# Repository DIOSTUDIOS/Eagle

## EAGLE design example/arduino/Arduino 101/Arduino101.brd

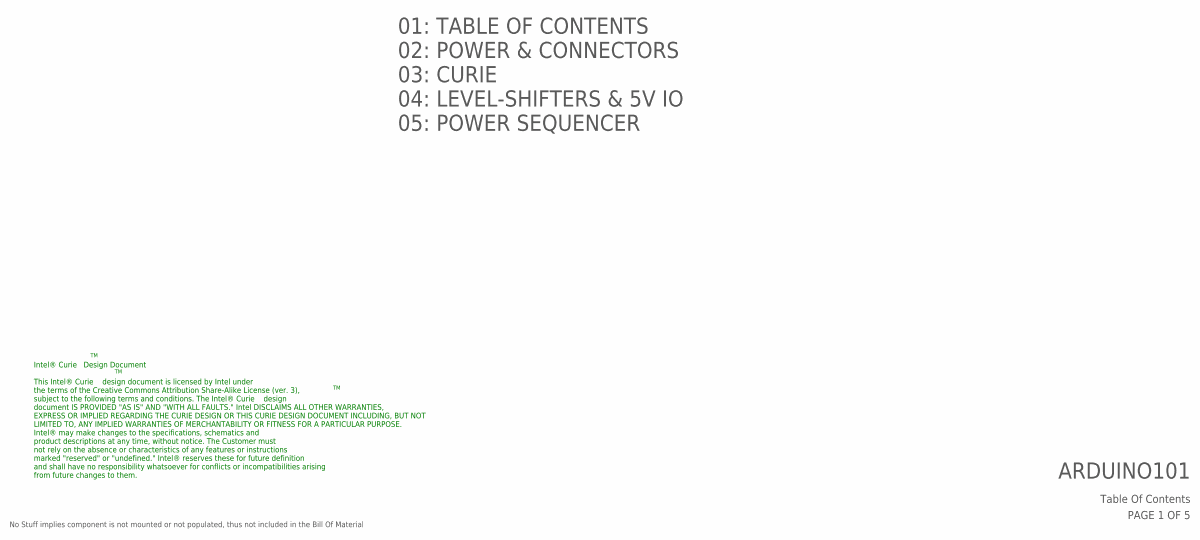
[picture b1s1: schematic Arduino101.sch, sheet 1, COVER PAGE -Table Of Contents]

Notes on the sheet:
Table Of Contents
PAGE 1 OF 5
ARDUINO101
No Stuff implies component is not mounted or not populated, thus not included in the Bill Of Material
01: TABLE OF CONTENTS
02: POWER & CONNECTORS
03: CURIE
04: LEVEL-SHIFTERS & 5V IO
05: POWER SEQUENCER
Intel® Curie Design Document This Intel® Curie design document is licensed by Intel under the terms of the Creative Commons Attribution Share-Alike License (ver. 3), subject to the following terms and conditions. The Intel® Curie design document IS PROVIDED "AS IS" AND "WITH ALL FAULTS." Intel DISC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

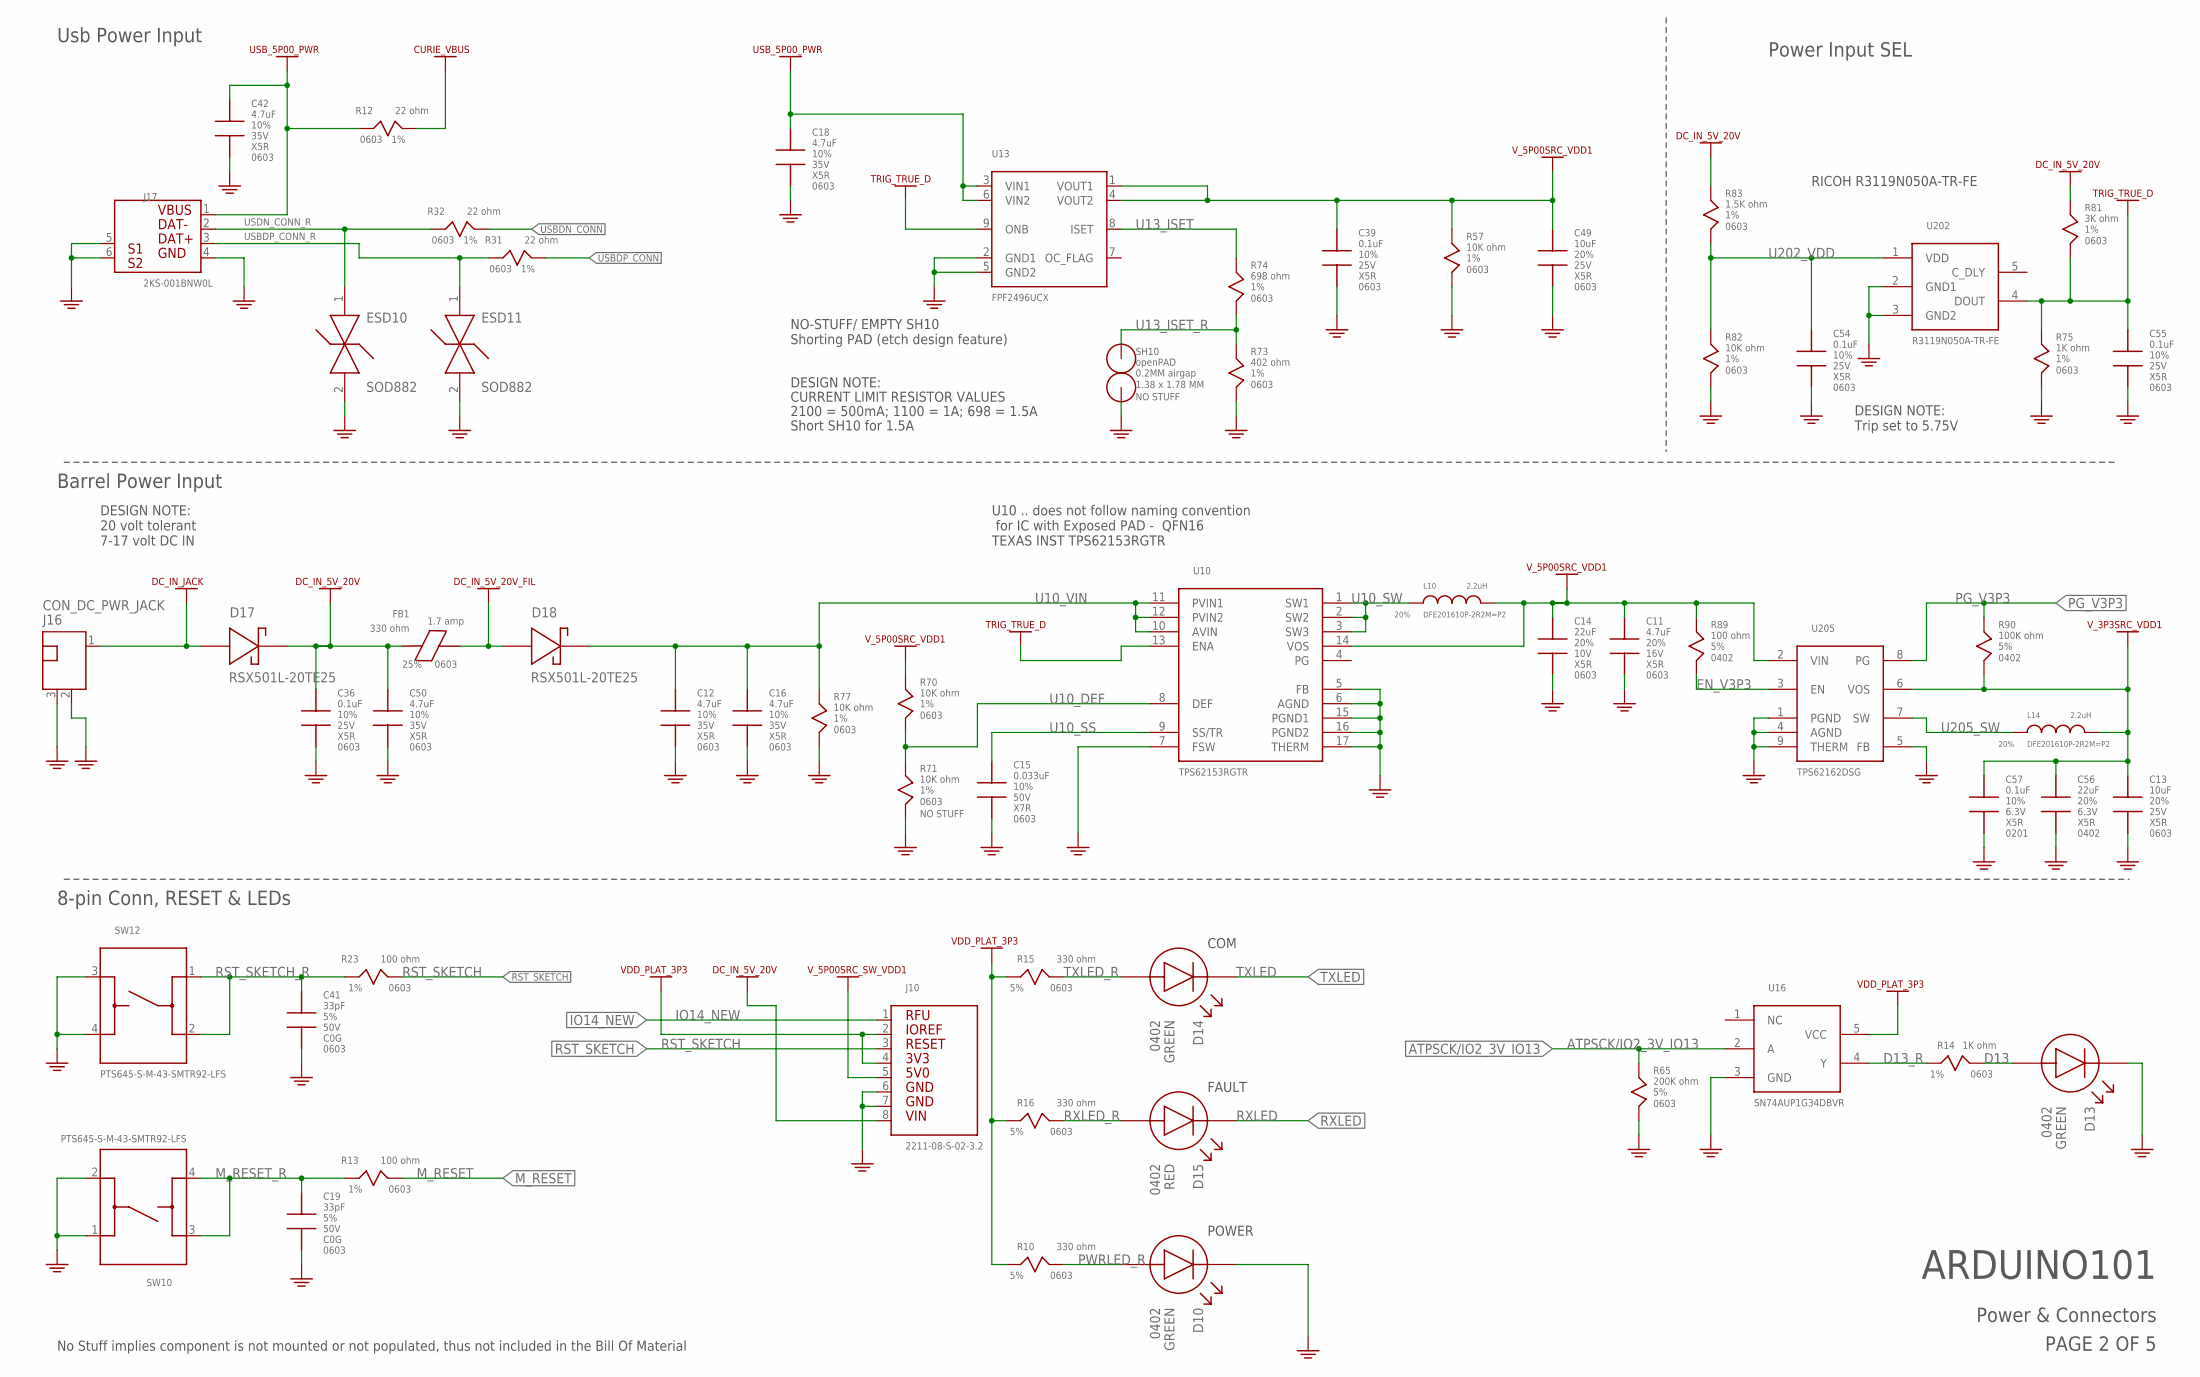
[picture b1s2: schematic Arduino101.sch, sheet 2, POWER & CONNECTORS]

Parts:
C11, C12, C16, C18, C42, C50: 4.7uF; 0603X90H
C13, C49: 10uF; 0603X90H
C14: 22uF; 0603X90H
C15: 0.033uF; 0603X90H
C19, C41: 33pF; 0603X90H
C36, C39, C54, C55: 0.1uF; 0603X90H
C56: 22uF; CAP0402
C57: 0.1uF; CAP0201
D10, D13, D14: LED_SML-P12PTT86; LED_100X60X25H_SMLP13
D15: LED_SML-P11UTT86; LED_100X60X25H_SMLP13
D17, D18: DIO_RSX501L-20TE25; DIO2_450X260X220H
ESD10, ESD11: PESD5V0X1BCAL,315; DIO_SOD882
FB1: FERRITE_BEAD_0603_BLM18KG331SN1D; 0603X90H
J10: CON_1X8_2211-08-S-02-3.2; CONF1X8-254P_2104X240X850H_TH
J16: CON_DC_PWR_JACK; CON_JACK_880X1350X1135H_EJ508A
J17: CON_USB_TYPE_B; CON_USB_1204X1650X1115_AUY1007
L10, L14: 2.2uH; 0806X100H
R10, R15, R16: 330 ohm; 0603X90H
R12, R31, R32: 22 ohm; 0603X90H
R13, R23: 100 ohm; 0603X90H
R14, R75: 1K ohm; 0603X90H
R57, R70, R71, R77, R82: 10K ohm; 0603X90H
R65: 200K ohm; 0603X90H
R73: 402 ohm; 0603X90H
R74: 698 ohm; 0603X90H
R81: 3K ohm; 0603X90H
R83: 1.5K ohm; 0603X90H
R89: 100 ohm; SMR0402
R90: 100K ohm; SMR0402
SH10: openPAD; SHORT_140X180
SW10, SW12: SWITCH_PTS645-S-M-43-SMTR92-LFS; SW4_600X600X430H_SM_PTS645
U10: TPS62153RGTR; QFN16-50P_300X300X100H_TR
U13: FPF2496UCX_WLCSP_VREG; BGA9_3X3-40P_121X121X63H
U16: SN74AUP1G34DBVR; SOT23-5_160X290X145H
U202: R3119-VREG; SOT23-5_160X290X120H
U205: TPS62162DSG; USON8_5MM_2X2MM-DIE

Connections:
ATPSCK/IO2_3V_IO13: R65.1, U16.2 (A); also elsewhere on the board
CURIE_VBUS: R12.2; also elsewhere on the board
D13: D13.1 (A), R14.2
D13_R: R14.1, U16.4 (Y)
DC_IN_5V_20V: C36.1, C50.1, D17.1, FB1.1, J10.8, R81.1, R83.1
DC_IN_5V_20V_FIL: D18.2, FB1.2
DC_IN_JACK: D17.2, J16.1; also elsewhere on the board
EN_V3P3: R89.2, U205.3 (EN)
GND: C11.2, C12.2, C13.2, C14.2, C15.2, C16.2, C18.2, C19.2, C36.2, C39.2, C41.2, C42.2, C49.2, C50.2, C54.2, C55.2, C56.2, C57.2, D10.2 (K), D13.2 (K), ESD10.2, ESD11.2, J10.6, J10.7, J16.2, J16.3, J17.4, J17.5, J17.6, R57.2, R65.2, R71.2, R73.2, R75.2, R77.2, R82.2, SH10.2, SW10.1, SW10.2, SW12.3, SW12.4, U10.5 (FB), U10.6 (AGND), U10.7 (FSW), U10.15 (PGND1), U10.16 (PGND2), U10.17 (THERM), U13.2 (GND1), U13.5 (GND2), U16.3 (GND), U202.2 (GND1), U202.3 (GND2), U205.1 (PGND), U205.4 (AGND), U205.5 (FB), U205.9 (THERM); also elsewhere on the board
IO14_NEW: J10.1; also elsewhere on the board
M_RESET: R13.2; also elsewhere on the board
M_RESET_R: C19.1, R13.1, SW10.3, SW10.4
PG_V3P3: R90.1, U205.8 (PG); also elsewhere on the board
PWRLED_R: D10.1 (A), R10.2
RST_SKETCH: J10.3, R23.2; also elsewhere on the board
RST_SKETCH_R: C41.1, R23.1, SW12.1, SW12.2
RXLED: D15.2 (K); also elsewhere on the board
RXLED_R: D15.1 (A), R16.2
TRIG_TRUE_D: C55.1, R75.1, R81.2, U10.13 (ENA), U13.9 (ONB), U202.4 (DOUT)
TXLED: D14.2 (K); also elsewhere on the board
TXLED_R: D14.1 (A), R15.2
U10_DEF: R70.2, R71.1, U10.8 (DEF)
U10_SS: C15.1, U10.9 (SS/TR)
U10_SW: L10.1, U10.1 (SW1), U10.2 (SW2), U10.3 (SW3)
U10_VIN: C12.1, C16.1, D18.1, R77.1, U10.10 (AVIN), U10.11 (PVIN1), U10.12 (PVIN2)
U13_ISET: R74.1, U13.8 (ISET)
U13_ISET_R: R73.1, R74.2, SH10.1
U202_VDD: C54.1, R82.1, R83.2, U202.1 (VDD)
U205_SW: L14.1, U205.7 (SW)
USBDN_CONN: R32.2; also elsewhere on the board
USBDP_CONN: R31.2; also elsewhere on the board
USBDP_CONN_R: ESD11.1, J17.3, R31.1
USB_5P00_PWR: C18.1, C42.1, J17.1, R12.1, U13.3 (VIN1), U13.6 (VIN2); also elsewhere on the board
USDN_CONN_R: ESD10.1, J17.2, R32.1
VDD_PLAT_3P3: J10.2, J10.4, R10.1, R15.1, R16.1, U16.5 (VCC); also elsewhere on the board
V_3P3SRC_VDD1: C13.1, C56.1, C57.1, L14.2, R90.2, U205.6 (VOS); also elsewhere on the board
V_5P00SRC_SW_VDD1: J10.5; also elsewhere on the board
V_5P00SRC_VDD1: C11.1, C14.1, C39.1, C49.1, L10.2, R57.1, R70.1, R89.1, U10.14 (VOS), U13.1 (VOUT1), U13.4 (VOUT2), U205.2 (VIN); also elsewhere on the board

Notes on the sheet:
Power & Connectors
PAGE 2 OF 5
ARDUINO101
Barrel Power Input
DESIGN NOTE:
CURRENT LIMIT RESISTOR VALUES
2100 = 500mA; 1100 = 1A; 698 = 1.5A
Usb Power Input
No Stuff implies component is not mounted or not populated, thus not included in the Bill Of Material
8-pin Conn, RESET & LEDs
Power Input SEL
DESIGN NOTE: Trip set to 5.75V
Short SH10 for 1.5A
DESIGN NOTE: 20 volt tolerant 7-17 volt DC IN
COM
FAULT
POWER
NO-STUFF/ EMPTY SH10 Shorting PAD (etch design feature)
RICOH R3119N050A-TR-FE
U10 .. does not follow naming convention for IC with Exposed PAD - QFN16 TEXAS INST TPS62153RGTR

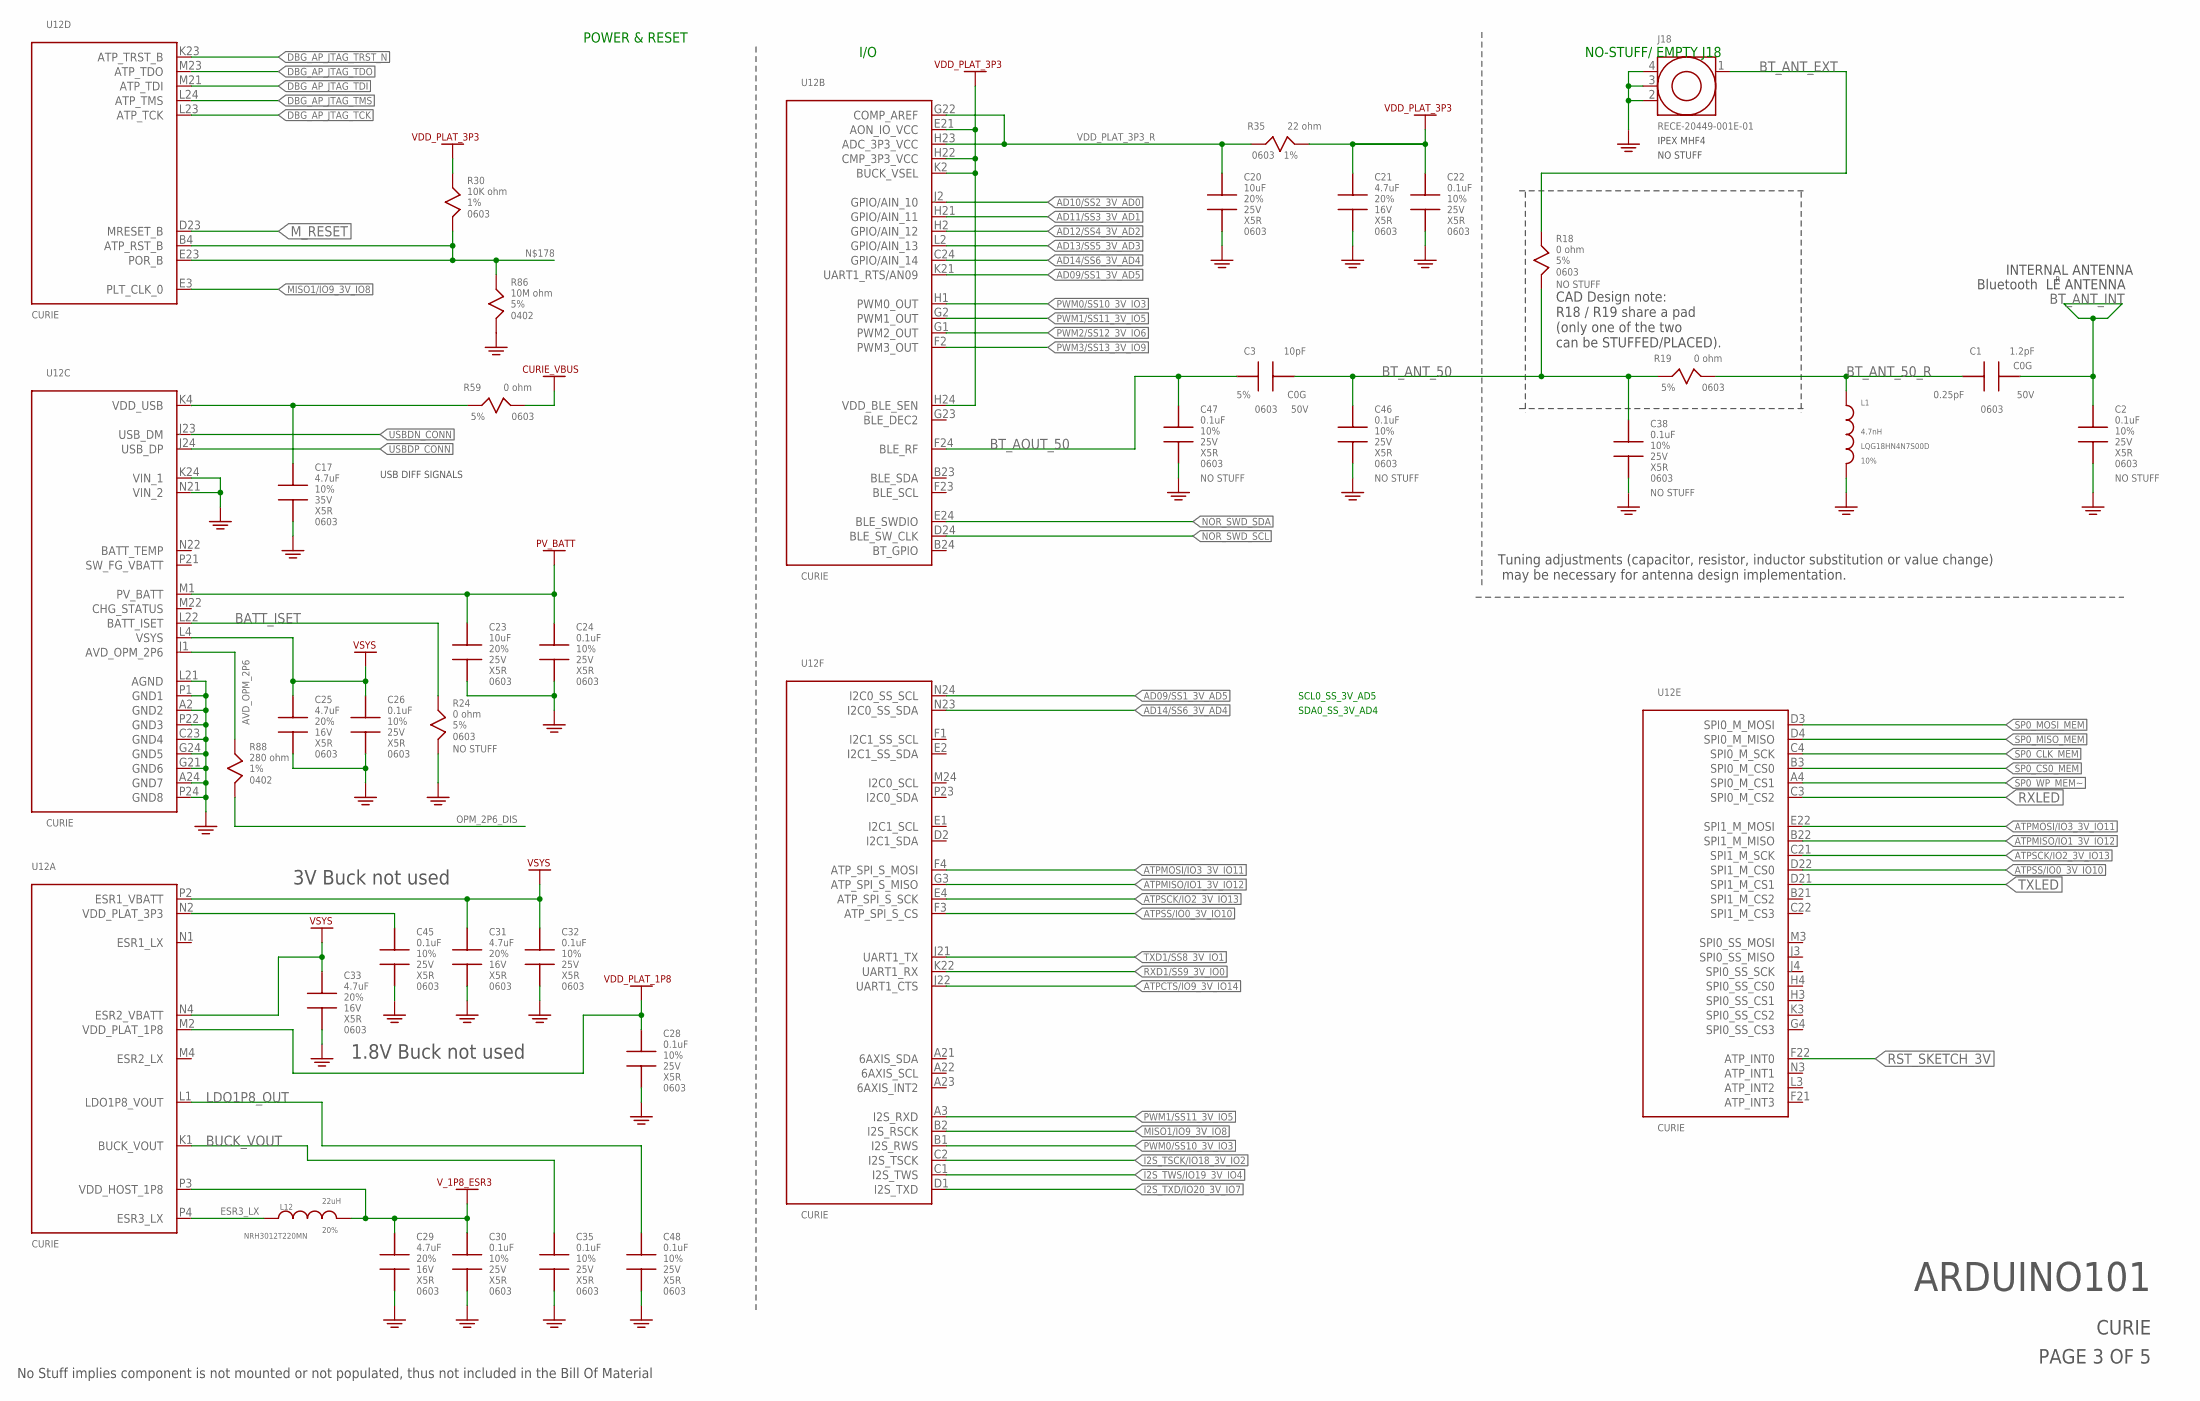
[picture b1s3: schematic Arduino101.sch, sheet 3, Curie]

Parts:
C1: 1.2pF; 0603X90H
C2, C22, C24, C26, C28, C30, C32, C35, C38, C45, C46, C47, C48: 0.1uF; 0603X90H
C3: 10pF; 0603X90H
C17, C21, C25, C29, C31, C33: 4.7uF; 0603X90H
C20, C23: 10uF; 0603X90H
J18: 20449-001E-01; CONN_COAX_MHF4
L1: 4.7nH; 0603X90H
L12: 22uH; COIL_300X300X120H_NRH3012
R18, R19, R24, R59: 0 ohm; 0603X90H
R30: 10K ohm; 0603X90H
R35: 22 ohm; 0603X90H
R86: 10M ohm; SMR0402
R88: 280 ohm; SMR0402
U12: CURIE; BGA111_14X24-57P_805X1100X150H

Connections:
AD09/SS1_3V_AD5: U12.K21 (UART1_RTS/AN09), U12.N24 (I2C0_SS_SCL); also elsewhere on the board
AD10/SS2_3V_AD0: U12.J2 (GPIO/AIN_10); also elsewhere on the board
AD11/SS3_3V_AD1: U12.H21 (GPIO/AIN_11); also elsewhere on the board
AD12/SS4_3V_AD2: U12.H2 (GPIO/AIN_12); also elsewhere on the board
AD13/SS5_3V_AD3: U12.L2 (GPIO/AIN_13); also elsewhere on the board
AD14/SS6_3V_AD4: U12.C24 (GPIO/AIN_14), U12.N23 (I2C0_SS_SDA); also elsewhere on the board
ATPCTS/IO9_3V_IO14: U12.J22 (UART1_CTS); also elsewhere on the board
ATPMISO/IO1_3V_IO12: U12.B22 (SPI1_M_MISO), U12.G3 (ATP_SPI_S_MISO); also elsewhere on the board
ATPMOSI/IO3_3V_IO11: U12.E22 (SPI1_M_MOSI), U12.F4 (ATP_SPI_S_MOSI); also elsewhere on the board
ATPSCK/IO2_3V_IO13: U12.C21 (SPI1_M_SCK), U12.E4 (ATP_SPI_S_SCK); also elsewhere on the board
ATPSS/IO0_3V_IO10: U12.D22 (SPI1_M_CS0), U12.F3 (ATP_SPI_S_CS); also elsewhere on the board
AVD_OPM_2P6: R88.1, U12.J1 (AVD_OPM_2P6)
BATT_ISET: R24.1, U12.L22 (BATT_ISET)
BT_ANT_50: C3.2, C38.1, C46.1, R18.2, R19.1
BT_ANT_50_R: C1.1, L1.1, R19.2
BT_ANT_EXT: J18.1, R18.1
BT_ANT_INT: C1.2, C2.1
BT_AOUT_50: C3.1, C47.1, U12.F24 (BLE_RF)
BUCK_VOUT: C35.1, U12.K1 (BUCK_VOUT)
CURIE_VBUS: R59.2; also elsewhere on the board
DBG_AP_JTAG_TCK: U12.L23 (ATP_TCK); also elsewhere on the board
DBG_AP_JTAG_TDI: U12.M21 (ATP_TDI); also elsewhere on the board
DBG_AP_JTAG_TDO: U12.M23 (ATP_TDO); also elsewhere on the board
DBG_AP_JTAG_TMS: U12.L24 (ATP_TMS); also elsewhere on the board
DBG_AP_JTAG_TRST_N: U12.K23 (ATP_TRST_B); also elsewhere on the board
ESR3_LX: L12.1, U12.P4 (ESR3_LX)
GND: C2.2, C17.2, C20.2, C21.2, C22.2, C23.2, C24.2, C25.2, C26.2, C28.2, C29.2, C30.2, C31.2, C32.2, C33.2, C35.2, C38.2, C45.2, C46.2, C47.2, C48.2, J18.2, J18.3, J18.4, L1.2, R24.2, R86.2, U12.A2 (GND2), U12.A24 (GND7), U12.C23 (GND4), U12.G21 (GND6), U12.G24 (GND5), U12.K24 (VIN_1), U12.L21 (AGND), U12.N21 (VIN_2), U12.P1 (GND1), U12.P22 (GND3), U12.P24 (GND8); also elsewhere on the board
I2S_TSCK/IO18_3V_IO2: U12.C2 (I2S_TSCK); also elsewhere on the board
I2S_TWS/IO19_3V_IO4: U12.C1 (I2S_TWS); also elsewhere on the board
I2S_TXD/IO20_3V_IO7: U12.D1 (I2S_TXD); also elsewhere on the board
LDO1P8_OUT: C48.1, U12.L1 (LDO1P8_VOUT)
MISO1/IO9_3V_IO8: U12.B2 (I2S_RSCK), U12.E3 (PLT_CLK_0); also elsewhere on the board
M_RESET: U12.D23 (MRESET_B); also elsewhere on the board
unnamed: C17.1, R59.1, U12.K4 (VDD_USB)
unnamed: C45.1, U12.N2 (VDD_PLAT_3P3)
unnamed 65: R30.2, R86.1, U12.B4 (ATP_RST_B), U12.E23 (POR_B); also elsewhere on the board
NOR_SWD_SCL: U12.D24 (BLE_SW_CLK); also elsewhere on the board
NOR_SWD_SDA: U12.E24 (BLE_SWDIO); also elsewhere on the board
OPM_2P6_DIS: R88.2; also elsewhere on the board
PV_BATT: C23.1, C24.1, U12.M1 (PV_BATT)
PWM0/SS10_3V_IO3: U12.B1 (I2S_RWS), U12.H1 (PWM0_OUT); also elsewhere on the board
PWM1/SS11_3V_IO5: U12.A3 (I2S_RXD), U12.G2 (PWM1_OUT); also elsewhere on the board
PWM2/SS12_3V_IO6: U12.G1 (PWM2_OUT); also elsewhere on the board
PWM3/SS13_3V_IO9: U12.F2 (PWM3_OUT); also elsewhere on the board
RST_SKETCH_3V: U12.F22 (ATP_INT0); also elsewhere on the board
RXD1/SS9_3V_IO0: U12.K22 (UART1_RX); also elsewhere on the board
RXLED: U12.C3 (SPI0_M_CS2); also elsewhere on the board
SP0_CLK_MEM: U12.C4 (SPI0_M_SCK); also elsewhere on the board
SP0_CS0_MEM: U12.B3 (SPI0_M_CS0); also elsewhere on the board
SP0_MISO_MEM: U12.D4 (SPI0_M_MISO); also elsewhere on the board
SP0_MOSI_MEM: U12.D3 (SPI0_M_MOSI); also elsewhere on the board
SP0_WP_MEM~: U12.A4 (SPI0_M_CS1); also elsewhere on the board
TXD1/SS8_3V_IO1: U12.J21 (UART1_TX); also elsewhere on the board
TXLED: U12.D21 (SPI1_M_CS1); also elsewhere on the board
USBDN_CONN: U12.J23 (USB_DM); also elsewhere on the board
USBDP_CONN: U12.J24 (USB_DP); also elsewhere on the board
VDD_PLAT_1P8: C28.1, U12.M2 (VDD_PLAT_1P8)
VDD_PLAT_3P3: C21.1, C22.1, R30.1, R35.2, U12.E21 (AON_IO_VCC), U12.H22 (CMP_3P3_VCC), U12.H24 (VDD_BLE_SEN), U12.K2 (BUCK_VSEL); also elsewhere on the board
VDD_PLAT_3P3_R: C20.1, R35.1, U12.G22 (COMP_AREF), U12.H23 (ADC_3P3_VCC)
VSYS: C25.1, C26.1, C31.1, C32.1, C33.1, U12.L4 (VSYS), U12.N4 (ESR2_VBATT), U12.P2 (ESR1_VBATT); also elsewhere on the board
V_1P8_ESR3: C29.1, C30.1, L12.2, U12.P3 (VDD_HOST_1P8)

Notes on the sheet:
CURIE
PAGE 3 OF 5
ARDUINO101
SCL0_SS_3V_AD5
SDA0_SS_3V_AD4
No Stuff implies component is not mounted or not populated, thus not included in the Bill Of Material
I/O
Bluetooth LE ANTENNA
POWER & RESET
3V Buck not used
1.8V Buck not used
USB DIFF SIGNALS
INTERNAL ANTENNA
NO-STUFF/ EMPTY J18
CAD Design note: R18 / R19 share a pad (only one of the two can be STUFFED/PLACED).
Tuning adjustments (capacitor, resistor, inductor substitution or value change) may be necessary for antenna design implementation.

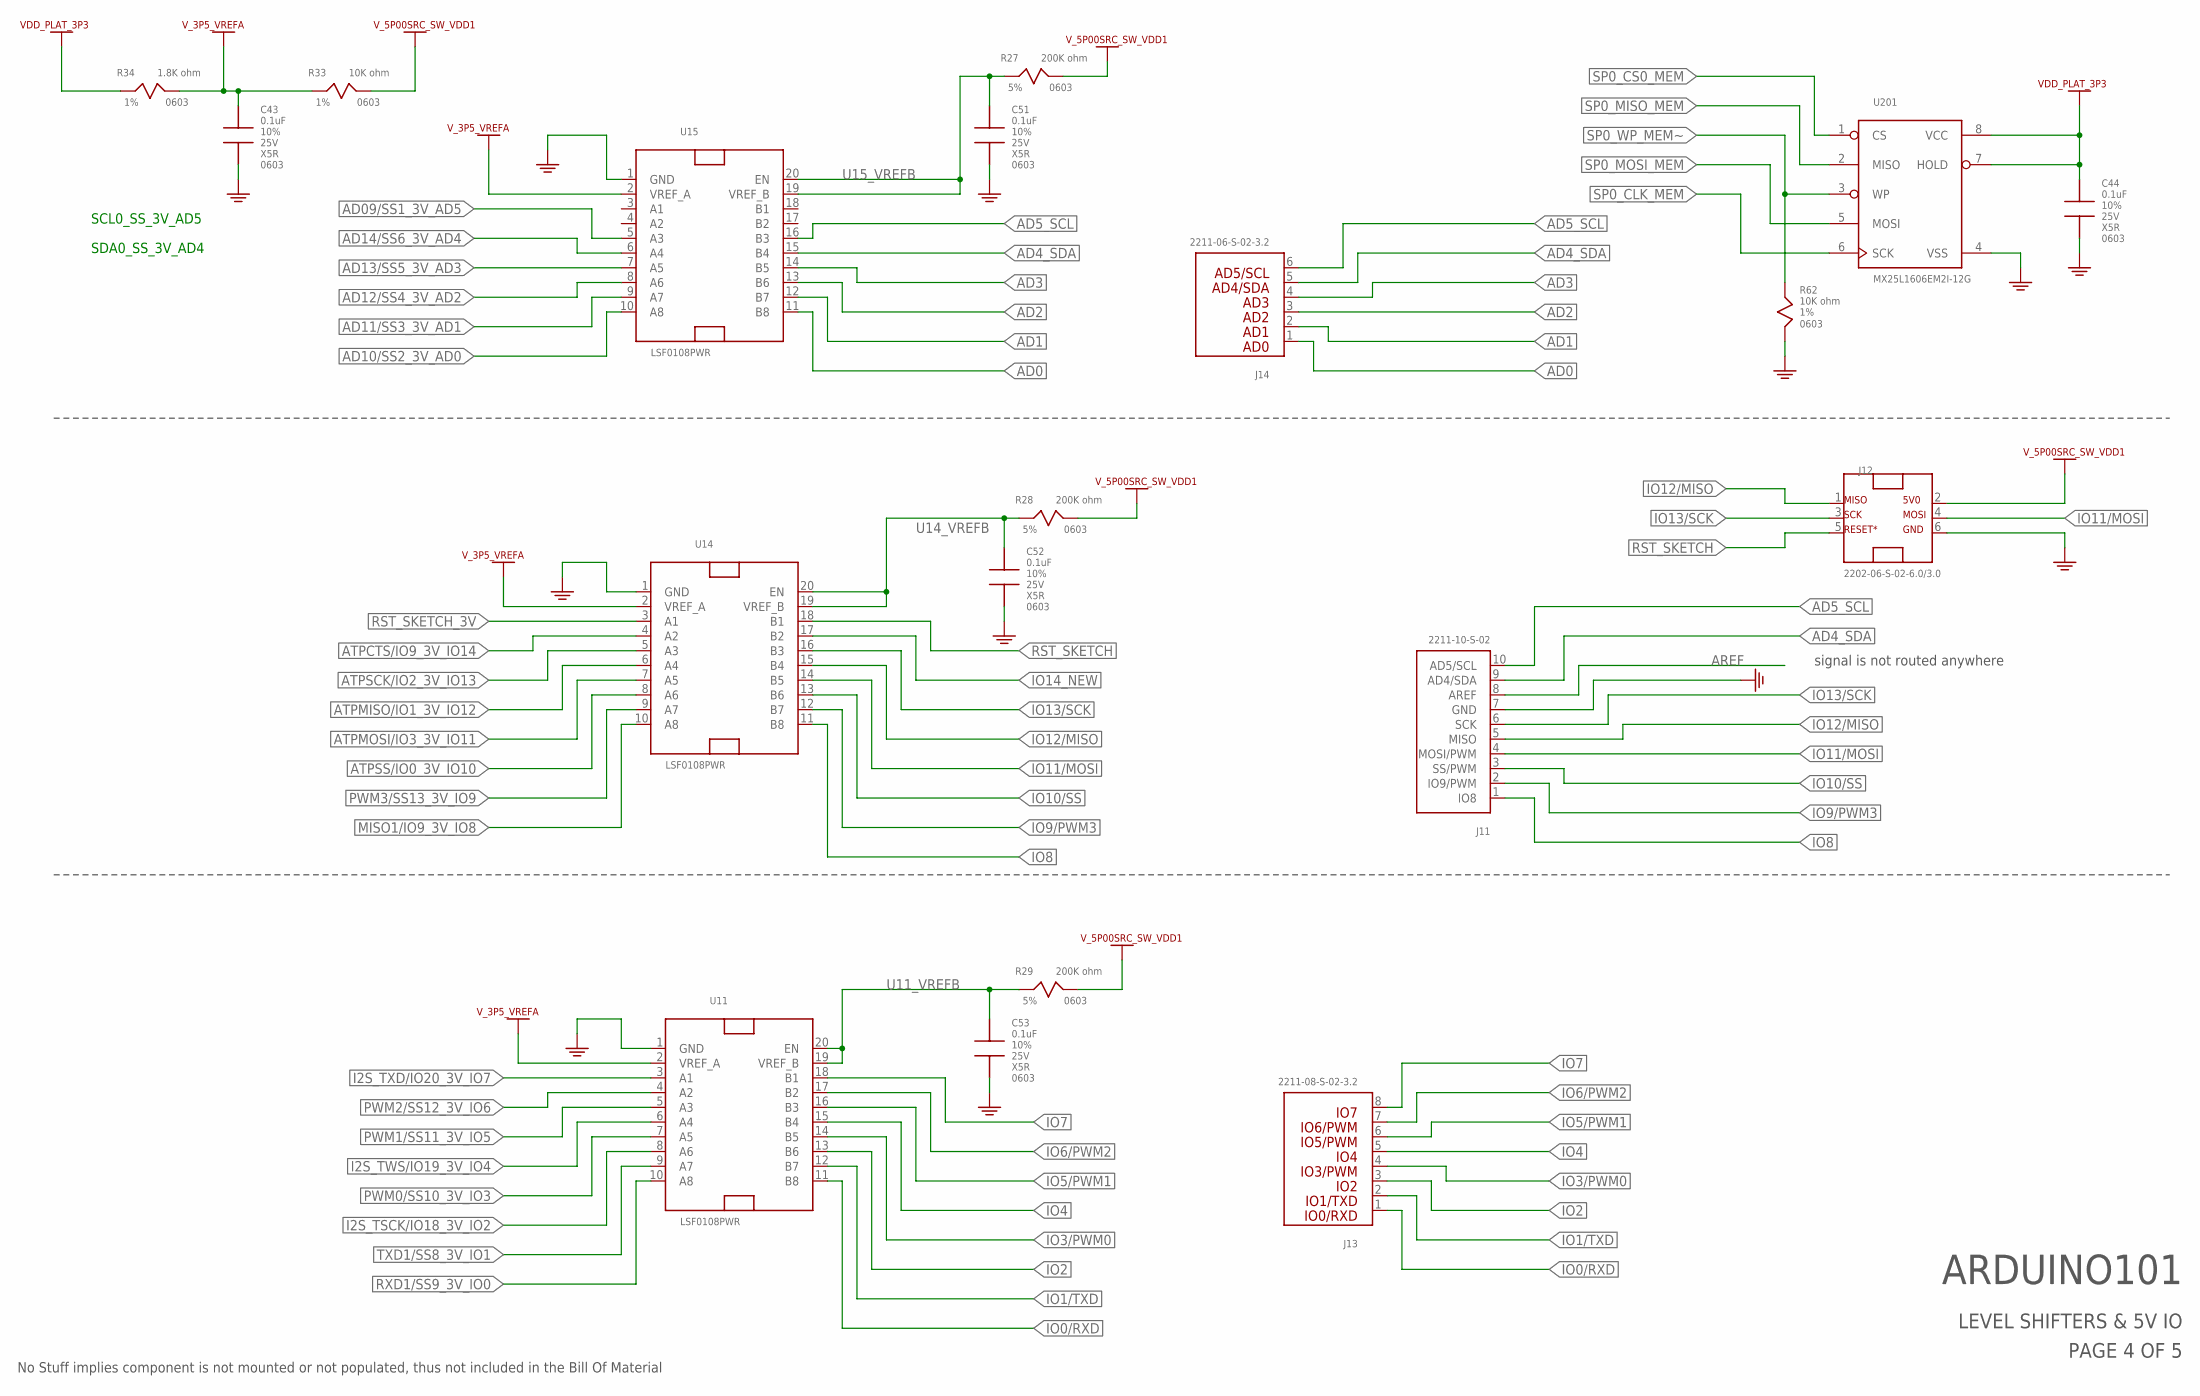
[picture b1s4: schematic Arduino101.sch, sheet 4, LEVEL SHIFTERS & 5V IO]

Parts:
C43, C44, C51, C52, C53: 0.1uF; 0603X90H
J11: CON_1X10_2211-10-S-02; CONF1X10-254P_2612X240X850H_TH
J12: CON_2X3_2202-06-S-02-6.0; CONM2X3-254P_762X500X860H_TH
J13: CON_1X8_2211-08-S-02-3.2_IO; CONF1X8-254P_2104X240X850H_TH
J14: CON_1X6_2211-06-S-02-3.2; CONF1X6-254P_1596X240X850H_TH
R27, R28, R29: 200K ohm; 0603X90H
R33, R62: 10K ohm; 0603X90H
R34: 1.8K ohm; 0603X90H
U11, U14, U15: IC_LSF0108PWR; SOIC20-65P_440X650X120H
U201: IC_MX25V1635FM2I_FLASH; SOIC8-127P_528X528X216H_1PRIMARY

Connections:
AD0: J14.1, U15.11 (B8)
AD1: J14.2, U15.12 (B7)
AD2: J14.3, U15.13 (B6)
AD3: J14.4, U15.14 (B5)
AD4_SDA: J11.9 (AD4/SDA), J14.5, U15.15 (B4)
AD5_SCL: J11.10 (AD5/SCL), J14.6, U15.16 (B3)
AD09/SS1_3V_AD5: U15.5 (A3); also elsewhere on the board
AD10/SS2_3V_AD0: U15.10 (A8); also elsewhere on the board
AD11/SS3_3V_AD1: U15.9 (A7); also elsewhere on the board
AD12/SS4_3V_AD2: U15.8 (A6); also elsewhere on the board
AD13/SS5_3V_AD3: U15.7 (A5); also elsewhere on the board
AD14/SS6_3V_AD4: U15.6 (A4); also elsewhere on the board
AREF: J11.8 (AREF)
ATPCTS/IO9_3V_IO14: U14.4 (A2); also elsewhere on the board
ATPMISO/IO1_3V_IO12: U14.6 (A4); also elsewhere on the board
ATPMOSI/IO3_3V_IO11: U14.7 (A5); also elsewhere on the board
ATPSCK/IO2_3V_IO13: U14.5 (A3); also elsewhere on the board
ATPSS/IO0_3V_IO10: U14.8 (A6); also elsewhere on the board
GND: C43.2, C44.2, C51.2, C52.2, C53.2, J11.7 (GND), J12.6, R62.2, U11.1 (GND), U14.1 (GND), U15.1 (GND), U201.4 (VSS); also elsewhere on the board
I2S_TSCK/IO18_3V_IO2: U11.8 (A6); also elsewhere on the board
I2S_TWS/IO19_3V_IO4: U11.6 (A4); also elsewhere on the board
I2S_TXD/IO20_3V_IO7: U11.3 (A1); also elsewhere on the board
IO0/RXD: J13.1, U11.11 (B8)
IO1/TXD: J13.2, U11.12 (B7)
IO2: J13.3, U11.13 (B6)
IO3/PWM0: J13.4, U11.14 (B5)
IO4: J13.5, U11.15 (B4)
IO5/PWM1: J13.6, U11.16 (B3)
IO6/PWM2: J13.7, U11.17 (B2)
IO7: J13.8, U11.18 (B1)
IO8: J11.1 (IO8), U14.11 (B8)
IO9/PWM3: J11.2 (IO9/PWM), U14.12 (B7)
IO10/SS: J11.3 (SS/PWM), U14.13 (B6)
IO11/MOSI: J11.4 (MOSI/PWM), J12.4, U14.14 (B5)
IO12/MISO: J11.5 (MISO), J12.1, U14.15 (B4)
IO13/SCK: J11.6 (SCK), J12.3, U14.16 (B3)
IO14_NEW: U14.17 (B2); also elsewhere on the board
MISO1/IO9_3V_IO8: U14.10 (A8); also elsewhere on the board
PWM0/SS10_3V_IO3: U11.7 (A5); also elsewhere on the board
PWM1/SS11_3V_IO5: U11.5 (A3); also elsewhere on the board
PWM2/SS12_3V_IO6: U11.4 (A2); also elsewhere on the board
PWM3/SS13_3V_IO9: U14.9 (A7); also elsewhere on the board
RST_SKETCH: J12.5, U14.18 (B1); also elsewhere on the board
RST_SKETCH_3V: U14.3 (A1); also elsewhere on the board
RXD1/SS9_3V_IO0: U11.10 (A8); also elsewhere on the board
SP0_CLK_MEM: U201.6 (SCK); also elsewhere on the board
SP0_CS0_MEM: U201.1 (CS); also elsewhere on the board
SP0_MISO_MEM: U201.2 (MISO); also elsewhere on the board
SP0_MOSI_MEM: U201.5 (MOSI); also elsewhere on the board
SP0_WP_MEM~: R62.1, U201.3 (WP); also elsewhere on the board
TXD1/SS8_3V_IO1: U11.9 (A7); also elsewhere on the board
U11_VREFB: C53.1, R29.1, U11.19 (VREF_B), U11.20 (EN)
U14_VREFB: C52.1, R28.1, U14.19 (VREF_B), U14.20 (EN)
U15_VREFB: C51.1, R27.1, U15.19 (VREF_B), U15.20 (EN)
VDD_PLAT_3P3: C44.1, R34.1, U201.7 (HOLD), U201.8 (VCC); also elsewhere on the board
V_3P5_VREFA: C43.1, R33.1, R34.2, U11.2 (VREF_A), U14.2 (VREF_A), U15.2 (VREF_A)
V_5P00SRC_SW_VDD1: J12.2, R27.2, R28.2, R29.2, R33.2; also elsewhere on the board

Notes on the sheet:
LEVEL SHIFTERS & 5V IO
PAGE 4 OF 5
ARDUINO101
No Stuff implies component is not mounted or not populated, thus not included in the Bill Of Material
SCL0_SS_3V_AD5
SDA0_SS_3V_AD4
signal is not routed anywhere

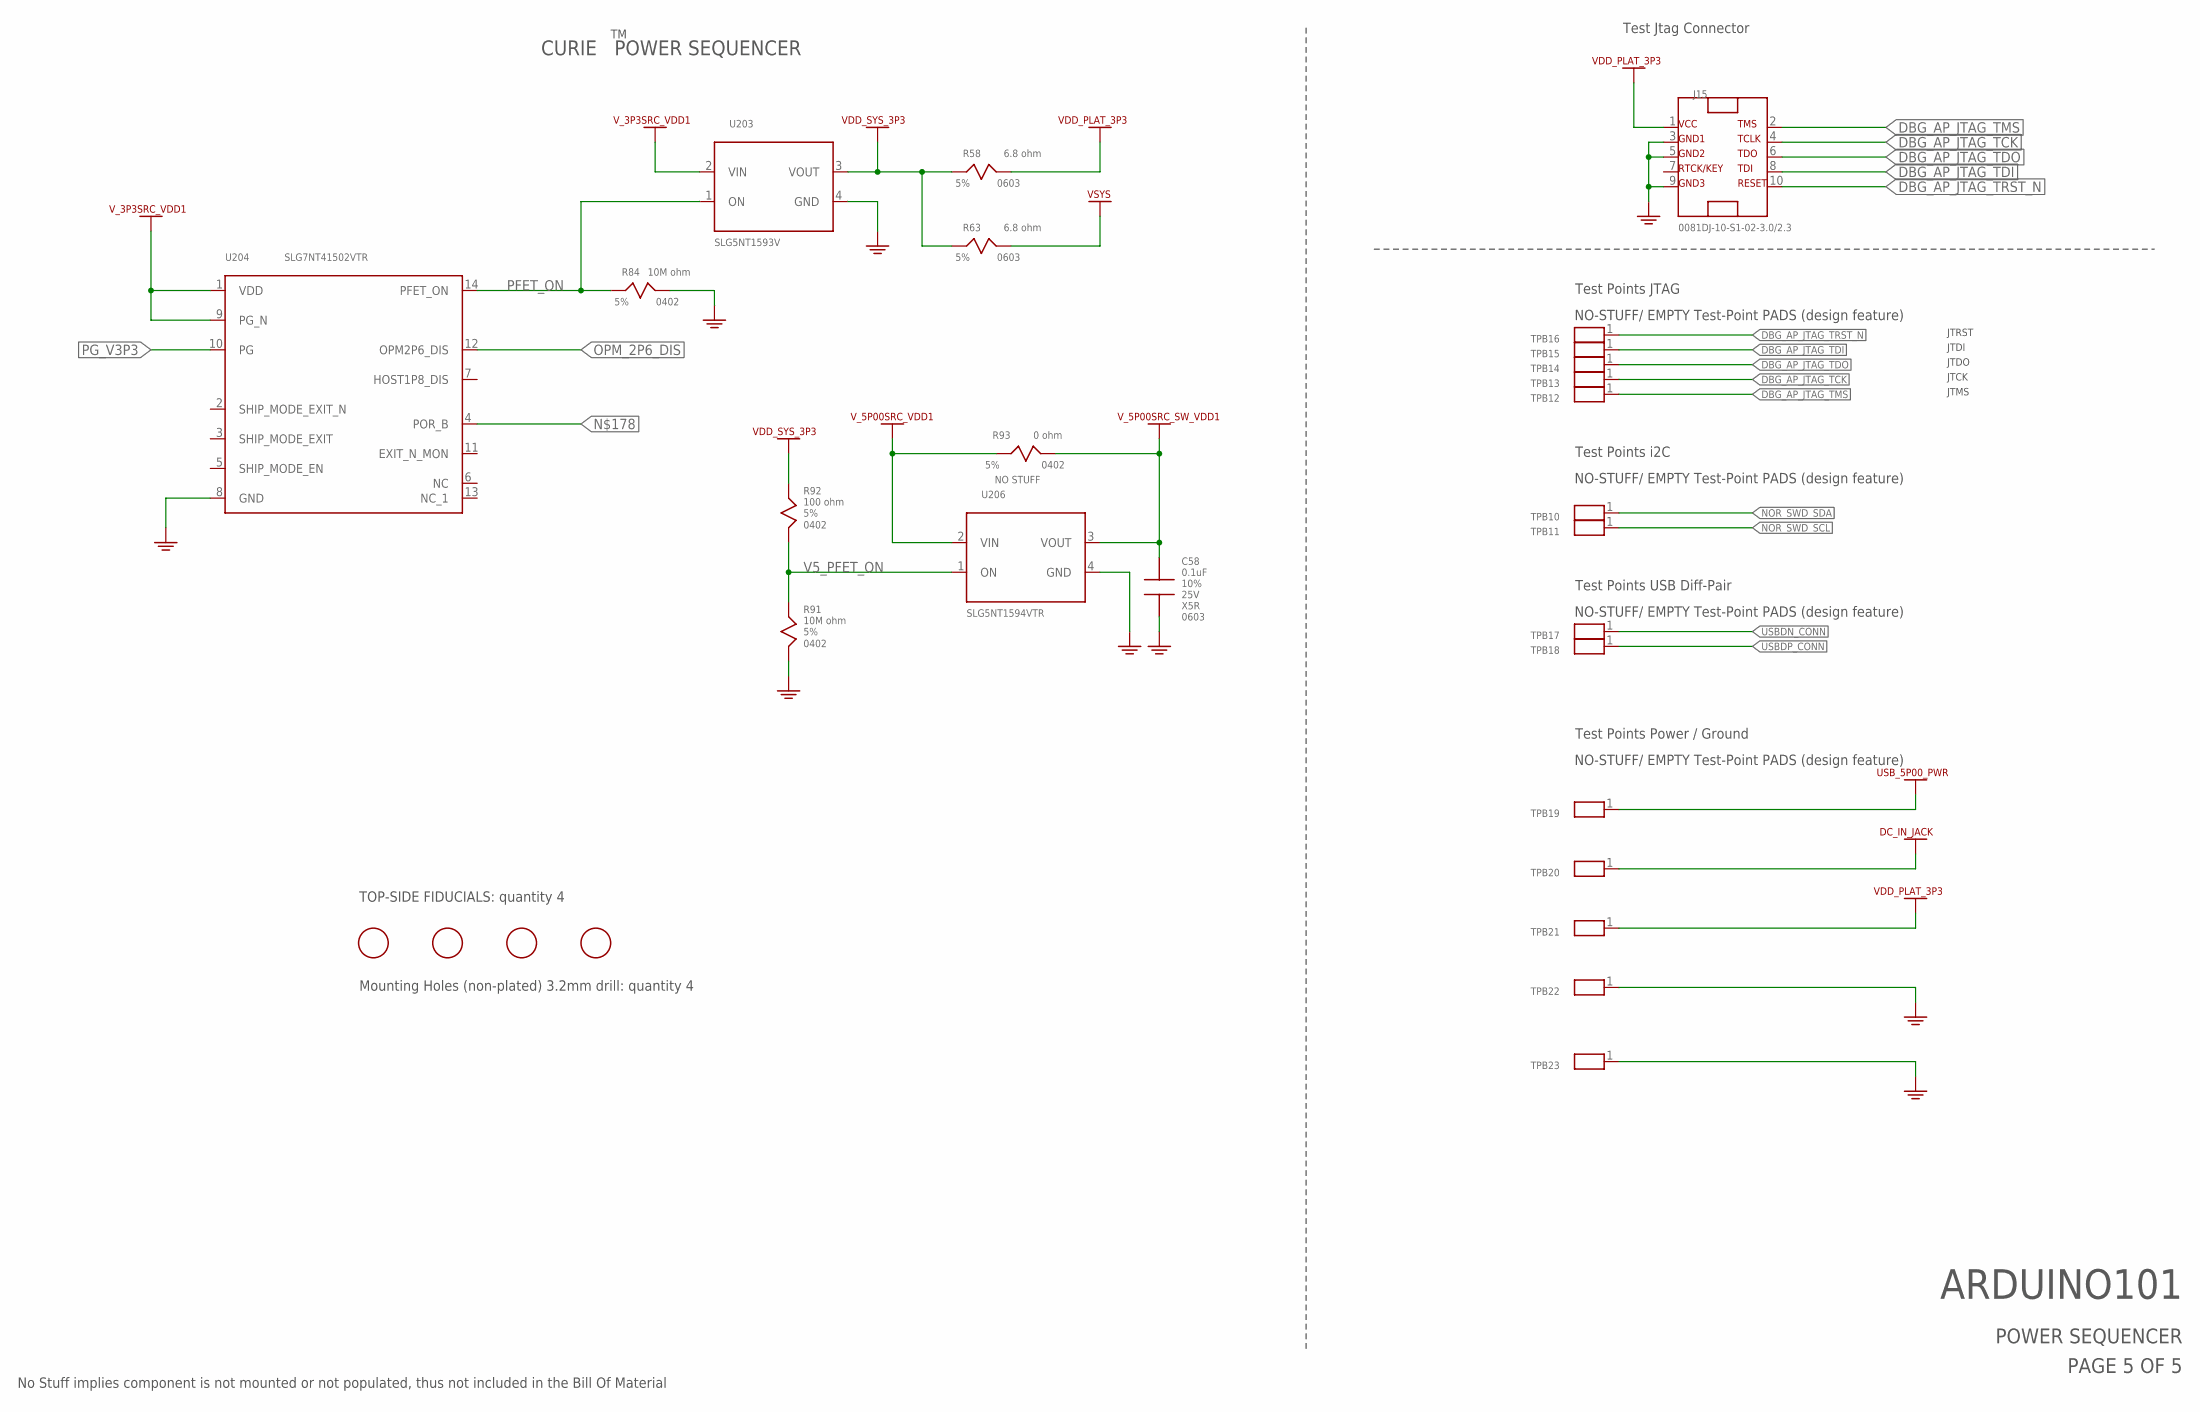
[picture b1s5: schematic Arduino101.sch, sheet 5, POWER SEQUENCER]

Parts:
C58: 0.1uF; 0603X90H
J15: CON_JTAG_20021111-00010T4LF; CONM2X5-127P_1270X559X533H
R58, R63: 6.8 ohm; 0603X90H
R84, R91: 10M ohm; SMR0402
R92: 100 ohm; SMR0402
R93: 0 ohm; SMR0402
TPB10, TPB11, TPB12, TPB13, TPB14, TPB15, TPB16, TPB17, TPB18, TPB19, TPB20, TPB21, TPB22, TPB23: TESTPAD; TP40
U203: SLG5NT1593V; LCC4_P4MM_SQ1MM
U204: SLG7NT41502VTR; STQFN14_2_40MA
U206: SLG5NT15944V; LCC4_P4MM_SQ1MM
U$1, U$2, U$3, U$4: FIDUCIAL_40

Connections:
DBG_AP_JTAG_TCK: J15.4, TPB13.1; also elsewhere on the board
DBG_AP_JTAG_TDI: J15.8, TPB15.1; also elsewhere on the board
DBG_AP_JTAG_TDO: J15.6, TPB14.1; also elsewhere on the board
DBG_AP_JTAG_TMS: J15.2, TPB12.1; also elsewhere on the board
DBG_AP_JTAG_TRST_N: J15.10, TPB16.1; also elsewhere on the board
DC_IN_JACK: TPB20.1; also elsewhere on the board
GND: C58.2, J15.3, J15.5, J15.9, R84.2, R91.2, TPB22.1, TPB23.1, U203.4 (GND), U204.8 (GND), U206.4 (GND); also elsewhere on the board
unnamed 65: U204.4 (POR_B); also elsewhere on the board
unnamed: R58.1, R63.1, R92.1, U203.3 (VOUT)
NOR_SWD_SCL: TPB11.1; also elsewhere on the board
NOR_SWD_SDA: TPB10.1; also elsewhere on the board
OPM_2P6_DIS: U204.12 (OPM2P6_DIS); also elsewhere on the board
PFET_ON: R84.1, U203.1 (ON), U204.14 (PFET_ON)
PG_V3P3: U204.10 (PG); also elsewhere on the board
USBDN_CONN: TPB17.1; also elsewhere on the board
USBDP_CONN: TPB18.1; also elsewhere on the board
USB_5P00_PWR: TPB19.1; also elsewhere on the board
V5_PFET_ON: R91.1, R92.2, U206.1 (ON)
VDD_PLAT_3P3: J15.1, R58.2, TPB21.1; also elsewhere on the board
VSYS: R63.2; also elsewhere on the board
V_3P3SRC_VDD1: U203.2 (VIN), U204.1 (VDD), U204.9 (PG_N); also elsewhere on the board
V_5P00SRC_SW_VDD1: C58.1, R93.2, U206.3 (VOUT); also elsewhere on the board
V_5P00SRC_VDD1: R93.1, U206.2 (VIN); also elsewhere on the board

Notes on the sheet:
POWER SEQUENCER
PAGE 5 OF 5
ARDUINO101
CURIE POWER SEQUENCER
Test Jtag Connector
JTRST
JTDI
JTDO
JTCK
JTMS
Test Points i2C
No Stuff implies component is not mounted or not populated, thus not included in the Bill Of Material
Test Points JTAG
Test Points USB Diff-Pair
Test Points Power / Ground
NO-STUFF/ EMPTY Test-Point PADS (design feature)
TOP-SIDE FIDUCIALS: quantity 4
Mounting Holes (non-plated) 3.2mm drill: quantity 4

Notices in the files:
example/arduino/Arduino NKR 485 Shield/MKR485ShieldV3.0.brd:
Copyright (c) 2016-2017 Arduino LLC.  All right reserved. EAGLE Design Rules
parts and their libraries:
Arduino-utility: Copyright (c) 2016-2017 Arduino LLC.  All right reserved.
Arduino-utility: This file is licensed under : CC-SA-BY-NC
SparkFun-Resistors: Licensing: Creative Commons ShareAlike 4.0 International - https://creativecommons.org/licenses/by-sa/4.0
